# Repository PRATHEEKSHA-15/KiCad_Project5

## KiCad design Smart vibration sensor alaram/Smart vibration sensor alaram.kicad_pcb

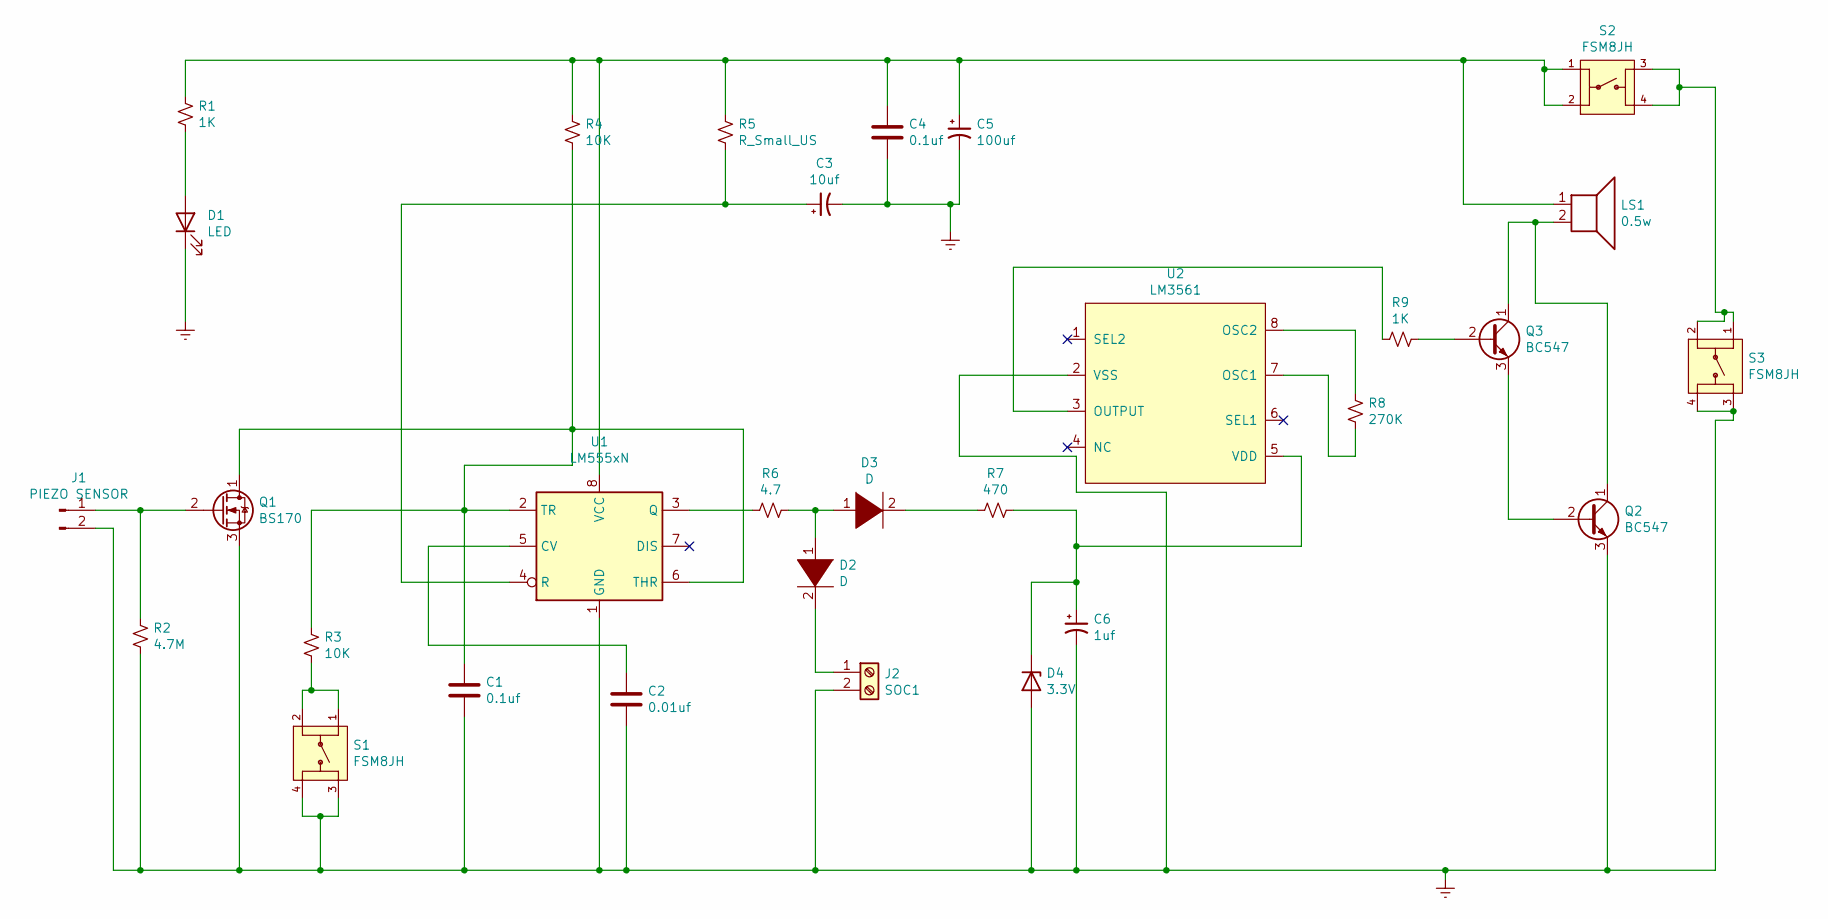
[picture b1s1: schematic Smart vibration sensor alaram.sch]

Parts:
C1: 0.1uf; SW_FSM8JH
C2: 0.01uf; C_Disc_D3.0mm_W1.6mm_P2.50mm
C3: 10uf; CP_Radial_D4.0mm_P2.00mm
C4: 0.1uf; C_Disc_D3.0mm_W1.6mm_P2.50mm
C5: 100uf; CP_Radial_D4.0mm_P2.00mm
C6: 1uf; CP_Radial_D4.0mm_P2.00mm
D1: LED; LED_D3.0mm
D2, D3: D; D_A-405_P2.54mm_Vertical_AnodeUp
D4: 3.3V; D_DO-35_SOD27_P2.54mm_Vertical_AnodeUp
J1: PIEZO SENSOR; PinHeader_1x02_P2.54mm_Vertical
J2: SOC1; PinSocket_1x02_P2.54mm_Vertical
LS1: 0.5w; PinHeader_1x02_P2.54mm_Vertical
Q1: BS170; TO-92_Inline
Q2, Q3: BC547; TO-92_Inline
R1, R9: 1K; R_Axial_DIN0204_L3.6mm_D1.6mm_P5.08mm_Horizontal
R2: 4.7M; R_Axial_DIN0204_L3.6mm_D1.6mm_P5.08mm_Horizontal
R3, R4: 10K; R_Axial_DIN0204_L3.6mm_D1.6mm_P5.08mm_Horizontal
R5: R_Small_US; R_Axial_DIN0204_L3.6mm_D1.6mm_P5.08mm_Horizontal
R6: 4.7; R_Axial_DIN0204_L3.6mm_D1.6mm_P5.08mm_Horizontal
R7: 470; R_Axial_DIN0204_L3.6mm_D1.6mm_P5.08mm_Horizontal
R8: 270K; R_Axial_DIN0204_L3.6mm_D1.6mm_P5.08mm_Horizontal
S1, S2, S3: FSM8JH; SW_FSM8JH; PARTREV C10
U1: LM555xN; DIP-8_W7.62mm
U2: LM3561; DIP-8_W7.62mm_LongPads

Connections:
Earth: C1.2, C2.2, C3.2, C4.2, C5.2, C6.2, D1.1 (K), D4.2 (A), J1.2, J2.2, Q1.3 (S), Q2.3 (E), R2.2, S1.3, S1.4, S3.3, S3.4, U1.1 (GND), U2.2 (VSS)
unnamed: C1.1, Q1.1 (D), R3.1, R4.2, U1.2 (TR), U1.6 (THR)
unnamed: C2.1, U1.5 (CV)
unnamed: C3.1, R5.2, U1.4 (R)
unnamed: C4.1, C5.1, LS1.1, R1.1, R4.1, R5.1, S2.1, S2.2, U1.8 (VCC)
unnamed: C6.1, D4.1 (K), R7.1, U2.5 (VDD)
unnamed: D1.2 (A), R1.2
unnamed: D2.1 (K), D3.1 (K), R6.1
unnamed: D2.2 (A), J2.1
unnamed: D3.2 (A), R7.2
unnamed: J1.1, Q1.2 (G), R2.1
unnamed: LS1.2, Q2.1 (C), Q3.1 (C)
unnamed: Q2.2 (B), Q3.3 (E)
unnamed: Q3.2 (B), R9.1
unnamed: R3.2, S1.1, S1.2
unnamed: R6.2, U1.3 (Q)
unnamed: R8.1, U2.7 (OSC1)
unnamed: R8.2, U2.8 (OSC2)
unnamed: R9.2, U2.3 (OUTPUT)
unnamed: S2.3, S2.4, S3.1, S3.2

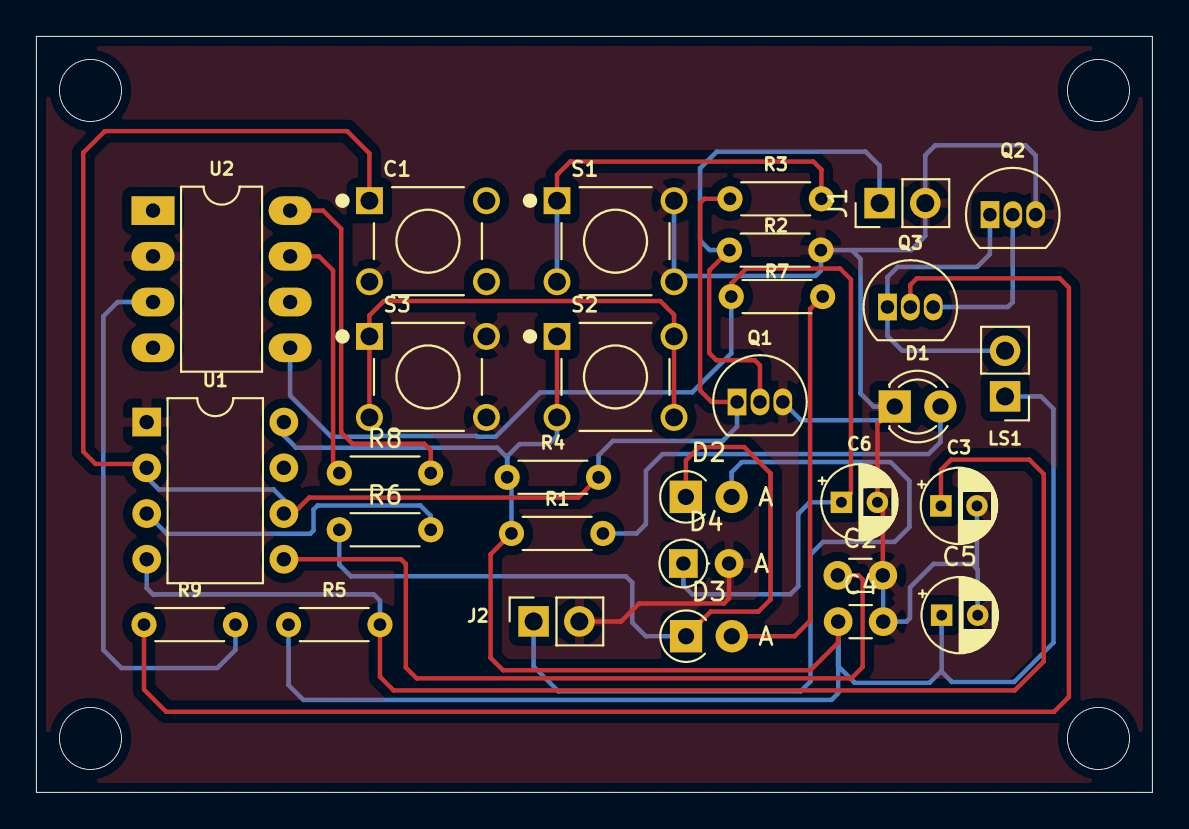
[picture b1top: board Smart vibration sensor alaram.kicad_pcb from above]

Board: 2 copper layers, 62.0 x 42.0 mm, 30 parts (0 on the bottom side), 20 nets.
